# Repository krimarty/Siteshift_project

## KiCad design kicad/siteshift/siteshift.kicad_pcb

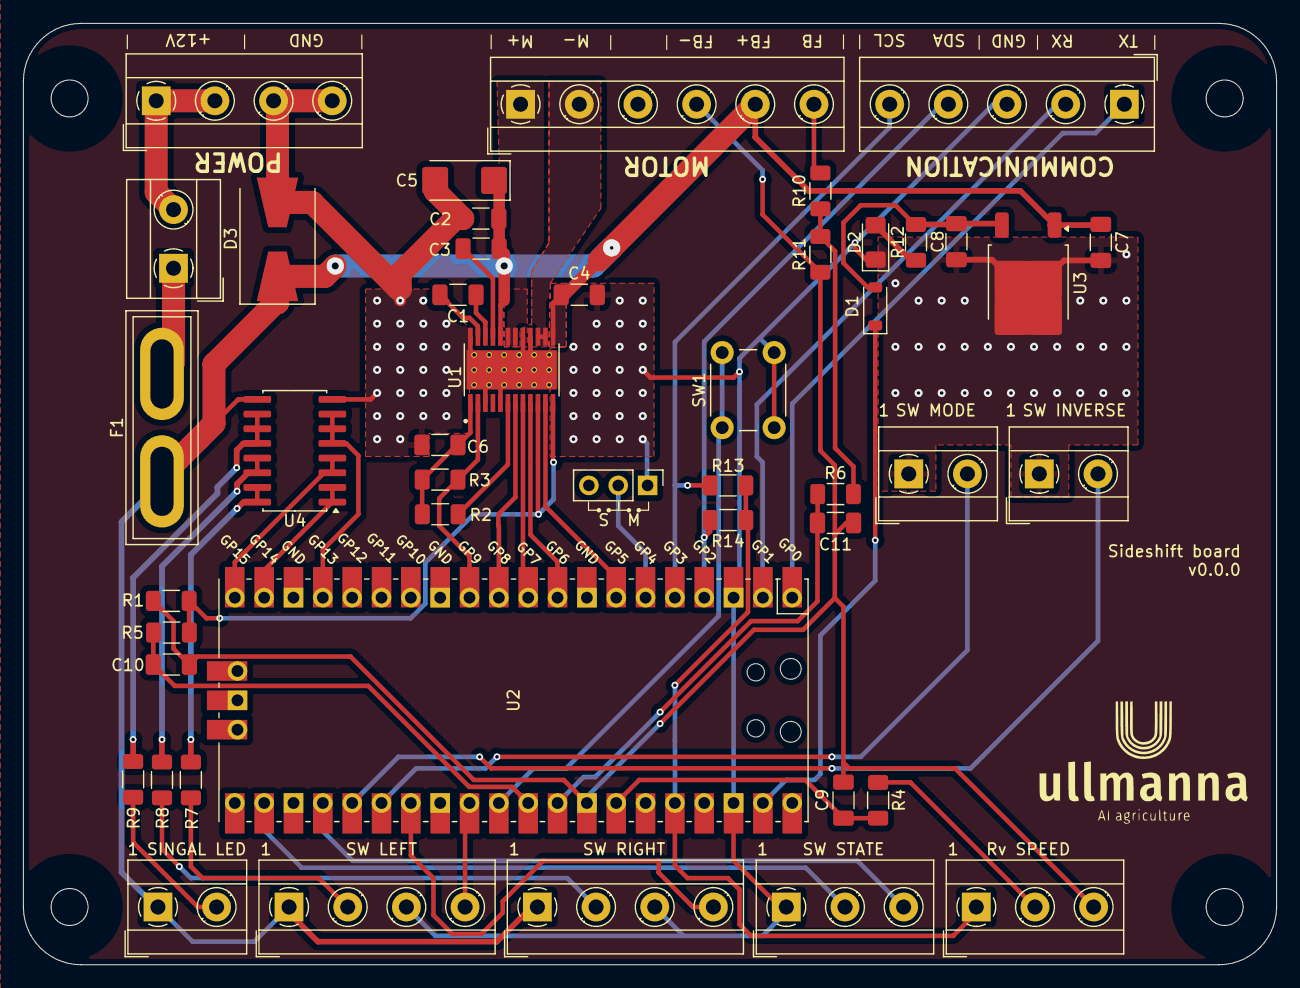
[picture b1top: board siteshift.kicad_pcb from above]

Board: 2 copper layers, 108.5 x 81.5 mm, 50 parts (0 on the bottom side), 49 nets.

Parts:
C1: 47 nF; C_1206_3216Metric_Pad1.33x1.80mm_HandSolder
C2, C6, C9, C11: 1 uF; C_1206_3216Metric_Pad1.33x1.80mm_HandSolder
C3, C4, C8: 0.1 uF; C_1206_3216Metric_Pad1.33x1.80mm_HandSolder
C5: >10 uF; CP_EIA-6032-20_AVX-F_Pad2.25x2.35mm_HandSolder
C7: 0.33 uF; C_1206_3216Metric_Pad1.33x1.80mm_HandSolder
C10: 3.3 nF; C_1206_3216Metric_Pad1.33x1.80mm_HandSolder
Communication1: Screw_Terminal_01x05; TerminalBlock_MetzConnect_Type101_RT01605HBWC_1x05_P5.08mm_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
D1: D_Schottky; D_SOD-123
D2: LED; D_1206_3216Metric_Pad1.42x1.75mm_HandSolder
D3: SS34A; D_SMB-SMC_Universal_Handsoldering
F1: Fuse; Fuse_Blade_ATO_directSolder
H3, H3#2, H3#3, H3#4: MountingHole; MountingHole_3.2mm_M3
IN_POWER1: Screw_Terminal_01x04; TerminalBlock_MetzConnect_Type101_RT01604HBWC_1x04_P5.08mm_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
LED_SIGNAL1: Screw_Terminal_01x02; TerminalBlock_MetzConnect_Type101_RT01602HBWC_1x02_P5.08mm_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
MASTER/SLAVE1: Jumper_2_Open; PinHeader_1x03_P2.54mm_Vertical
MOTOR1: Screw_Terminal_01x06; TerminalBlock_MetzConnect_Type101_RT01606HBWC_1x06_P5.08mm_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
R1: 360R; R_1206_3216Metric_Pad1.30x1.75mm_HandSolder
R2, R3, R4, R5, R6, R13, R14: 10k; R_1206_3216Metric_Pad1.30x1.75mm_HandSolder
R7, R8, R9: 470R; R_1206_3216Metric_Pad1.30x1.75mm_HandSolder
R10: 100k; R_1206_3216Metric_Pad1.30x1.75mm_HandSolder
R11: 36k; R_1206_3216Metric_Pad1.30x1.75mm_HandSolder
R12: 1k; R_1206_3216Metric_Pad1.30x1.75mm_HandSolder
RV_SPEED1: Screw_Terminal_01x03; TerminalBlock_MetzConnect_Type101_RT01603HBWC_1x03_P5.08mm_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
SW1: Reset; SW_PUSH_6mm_H5mm
SW_INVERSE2: Screw_Terminal_01x02; TerminalBlock_MetzConnect_Type101_RT01602HBWC_1x02_P5.08mm_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
SW_LEFT2: Screw_Terminal_01x04; TerminalBlock_MetzConnect_Type101_RT01604HBWC_1x04_P5.08mm_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
SW_MODE2: Screw_Terminal_01x02; TerminalBlock_MetzConnect_Type101_RT01602HBWC_1x02_P5.08mm_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
SW_PWR2: Screw_Terminal_01x02; TerminalBlock_MetzConnect_Type101_RT01602HBWC_1x02_P5.08mm_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
SW_RIGHT2: Screw_Terminal_01x04; TerminalBlock_MetzConnect_Type101_RT01604HBWC_1x04_P5.08mm_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
SW_STATE2: Screw_Terminal_01x03; TerminalBlock_MetzConnect_Type101_RT01603HBWC_1x03_P5.08mm_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
U1: DRV8873HPWPRQ1; SOP65P640X120-25N
U2: Pico; RPi_Pico_SMD_TH
U3: LM78M05_TO252; TO-252-2
U4: ULN2004A; SOIC-16W_5.3x10.2mm_P1.27mm

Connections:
+3.3V: R13.1, R14.1, RV_SPEED1.1, U2.36 (3V3)
+5V: C8.1, D1.2 (A), R12.2, U3.3 (VO)
+12V: C2.2, C3.1, C4.1, C5.1, C7.1, D3.1 (K), F1.1, LED_SIGNAL1.1, MOTOR1.5, SW_LEFT2.1, SW_RIGHT2.1, U1.13 (VM), U1.20 (VM), U3.1 (VI), U4.9 (COM)
AGND: C9.2, C10.2, C11.2, MOTOR1.4, R1.1, R11.1, RV_SPEED1.3, U2.33 (AGND)
DIR: U1.8 (PH/IN2), U2.10 (GPIO7)
DISABLE: U1.9 (DISABLE), U2.9 (GPIO6)
DVDD: C6.1, R2.1, R3.1, U1.1 (DVDD)
D_LEFT_PWR: R7.1, SW_LEFT2.2
D_RIGHT_PWR: R8.1, SW_RIGHT2.2
D_SIGNAL_PWR: LED_SIGNAL1.2, R9.1
GND: C3.2, C4.2, C5.2, C6.2, C7.2, C8.2, Communication1.3, D2.1 (K), D3.2 (A), IN_POWER1.3, IN_POWER1.4, MASTER/SLAVE1.1 (A), SW1.2, SW_INVERSE2.1, SW_LEFT2.3, SW_MODE2.1, SW_RIGHT2.3, SW_STATE2.1, U1.3 (MODE), U1.5 (NITRIP), U1.16 (SRC), U1.17 (SRC), U1.24 (GND), U1.25 (EXP), U1.P1 (EXP), U1.P2 (EXP), U1.P3 (EXP), U1.P4 (EXP), U1.P5 (EXP), U1.P6 (EXP), U1.P7 (EXP), U1.P8 (EXP), U1.P9 (EXP), U1.P10 (EXP), U1.P11 (EXP), U1.P12 (EXP), U1.P13 (EXP), U1.P14 (EXP), U1.P15 (EXP), U1.P16 (EXP), U1.P17 (EXP), U1.P18 (EXP), U2.3 (GND), U2.38 (GND), U3.2 (GND), U4.8 (GND)
I2C_SCL: Communication1.5, R13.2, U2.5 (GPIO3)
I2C_SDA: Communication1.4, R14.2, U2.4 (GPIO2)
IPROP: R1.2, R5.2, U1.10 (IPROPI1), U1.12 (IPROPI2)
IPROP_F: C10.1, R5.1, U2.31 (GPIO26_ADC0)
LED_LEFT_SW: U2.19 (GPIO14), U4.1 (I1), U4.2 (I2)
LED_RIGHT_SW: U2.20 (GPIO15), U4.3 (I3), U4.4 (I4)
LED_SIGNAL: U2.17 (GPIO13), U4.5 (I5), U4.6 (I6), U4.7 (I7)
MOTOR+: MOTOR1.1, U1.18 (OUT1), U1.19 (OUT1)
MOTOR-: MOTOR1.2, U1.14 (OUT2), U1.15 (OUT2)
MOTOR_FB: R6.2, R10.1, R11.2
MOTOR_FB_F: C11.1, R6.1, U2.32 (GPIO27_ADC1)
M/S: MASTER/SLAVE1.2 (B), U2.6 (GPIO4)
unnamed: D1.1 (K), U2.39 (VSYS)
unnamed: D2.2 (A), R12.1
unnamed: IN_POWER1.1, IN_POWER1.2, SW_PWR2.2
unnamed: MOTOR1.6, R10.2
unnamed: F1.2, SW_PWR2.1
unnamed: C1.1, U1.22 (CPH)
unnamed: C1.2, U1.23 (CPL)
unnamed: R2.2, U1.6 (NOL)
unnamed: C2.1, U1.21 (VCP)
unnamed: SW1.1, U2.30 (RUN)
unnamed: R7.2, U4.15 (O2), U4.16 (O1)
unnamed: R8.2, U4.13 (O4), U4.14 (O3)
unnamed: R9.2, U4.10 (O7), U4.11 (O6), U4.12 (O5)
PWM_SPEED: U1.7 (EN/IN1), U2.11 (GPIO8)
RV_SPEED: R4.2, RV_SPEED1.2
RV_SPEED_F: C9.1, R4.1, U2.34 (GPIO28_ADC2)
SW_INVERSE: SW_INVERSE2.2, U2.25 (GPIO19)
SW_LEFT: SW_LEFT2.4, U2.29 (GPIO22)
SW_MODE: SW_MODE2.2, U2.26 (GPIO20)
SW_RIGHT: SW_RIGHT2.4, U2.27 (GPIO21)
SW_STATE_MAN: SW_STATE2.3, U2.24 (GPIO18)
SW_STATE_SEQ: SW_STATE2.2, U2.22 (GPIO17)
UART_RX: Communication1.2, U2.2 (GPIO1)
UART_TX: Communication1.1, U2.1 (GPIO0)
nFAULT: R3.2, U1.2 (NFAULT), U2.12 (GPIO9)
nSLEEP: U1.11 (NSLEEP), U2.7 (GPIO5)

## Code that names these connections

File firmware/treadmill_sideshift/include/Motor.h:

/* =============================================================
 * Project:   treadmill_sideshift
 * File:      Motor.h
 * Author:    Martin Kriz
 * Company:   Ullmanna s.r.o.
 * Created:   2025-08-20
 * -------------------------------------------------------------
 * Description:
 *   This header defines the Motor class, which provides an interface
 *   to control a motor using the DRV8873H driver. 
 *   Designed for Raspberry Pi Pico 2 and the Sideshift Board v0.0.0.
 *
 * Notes:
 * ============================================================= */

#pragma once
#include <Arduino.h>

constexpr int NSLEEP  = 5;
constexpr int DISABLE = 6;
constexpr int PH     = 7;
constexpr int EN     = 8;
constexpr int NFAULT  = 9;

class Motor {
private:
    int _nSleep, _disable, _ph, _en, _nFault;
    int16_t _currentDuty = 0;
    int16_t _targetDuty = 0;
    uint32_t _lastUpdate = 0;
    uint16_t _rampDelay = 10;

    bool _isInverse = false;

    void setPwmFreq(uint32_t freq = 25000) {
        analogWriteFreq(freq);
    }

    void dutyUpdate_worker() {
        if (_currentDuty == _targetDuty) return;
        if (millis() - _lastUpdate >= _rampDelay) {
            if (_currentDuty < _targetDuty) {
                _currentDuty++;
            } else {
                _currentDuty--;
            }
            if (_currentDuty < 0) {
                digitalWrite(_ph, LOW);
            } else if (_currentDuty > 0) {
                digitalWrite(_ph, HIGH);
            }
            analogWrite(_en, map(abs(_currentDuty), 0, 100, 0, 255));
            _lastUpdate = millis();
        }
    }
public:
    Motor()
        : _nSleep(NSLEEP), _disable(DISABLE), _ph(PH), _en(EN), _nFault(NFAULT), _isInverse(false) {}

    Motor(int nSleep, int disable, int ph, int en, int nFault)
        : _nSleep(nSleep), _disable(disable), _ph(ph), _en(en), _nFault(nFault), _isInverse(false) {}

    void begin() {
        pinMode(_nSleep, OUTPUT);
        pinMode(_disable, OUTPUT);
        pinMode(_ph, OUTPUT);
        pinMode(_en, OUTPUT);
        setPwmFreq();
        pinMode(_nFault, INPUT);
        wake();
        enable();
        stop();
    }

    void dutyUpdate() {
        dutyUpdate_worker();
    }

    void wake() {
        digitalWrite(_nSleep, HIGH);
    }

    void sleep() {
        digitalWrite(_nSleep, LOW);
    }

    void enable() {
        digitalWrite(_disable, LOW); 
    }

    void disable() {
        digitalWrite(_disable, HIGH);
    }

    void left(int16_t duty) {
        if (duty > 100) {duty = 100;}
        if (_isInverse) {
            _targetDuty = duty;
        } else {
            _targetDuty = -duty;
        }
    }

    void right(int16_t duty) {
        if (duty > 100) {duty = 100;}
        if (_isInverse) {
            _targetDuty = -duty;
        }
        else {
            _targetDuty = duty;
        }
    }

    void stop() {
        _targetDuty = 0;
    }

    void resetFault() {
        digitalWrite(_nSleep, LOW);
        delayMicroseconds(12); 
        digitalWrite(_nSleep, HIGH);

    }
    bool isFault() {
        return digitalRead(_nFault) == LOW;
    }

    void setInverse(bool inverse) {
        _isInverse = inverse;
    }

};

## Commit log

2025-07-12 schematic update
2025-07-12 Wire power distribution
2025-07-12 Assign footprints
2025-07-13 first pcb design
2025-07-14 PCB design update
2025-07-14 Changed orientation
2025-07-14 Changed name
2025-07-15 First code setup
2025-07-17 Motor class update
2025-07-17 Add class for buttons and communication
2025-07-17 Add hardware classes
2025-07-17 Cummunication via define
2025-07-17 Cummunication by modern cpp
2025-07-18 communication + calibration state
2025-07-18 manual and seq state
2025-07-19 Random mode + LEDs
2025-07-19 Add inverse mode
2025-07-27 Add hardware test codes
2025-07-28 Communication test
2025-08-15 Motor class tested
2025-08-15 User interface tested
2025-08-15 Motor feedback tested
2025-08-15 random test
2025-08-19 sideshift test finished
2025-08-20 Add documentation header
2025-08-23 final code test
2025-08-24 Add readme
2025-08-27 add documentation
